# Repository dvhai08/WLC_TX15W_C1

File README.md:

# WLC_TX15W_C1
  Wireless Charging (WLC) MP A11 Power Transmitter
  1. **WLC1115 wireless power Tx simplified diagram**
  
  2. **PCB 3D view**

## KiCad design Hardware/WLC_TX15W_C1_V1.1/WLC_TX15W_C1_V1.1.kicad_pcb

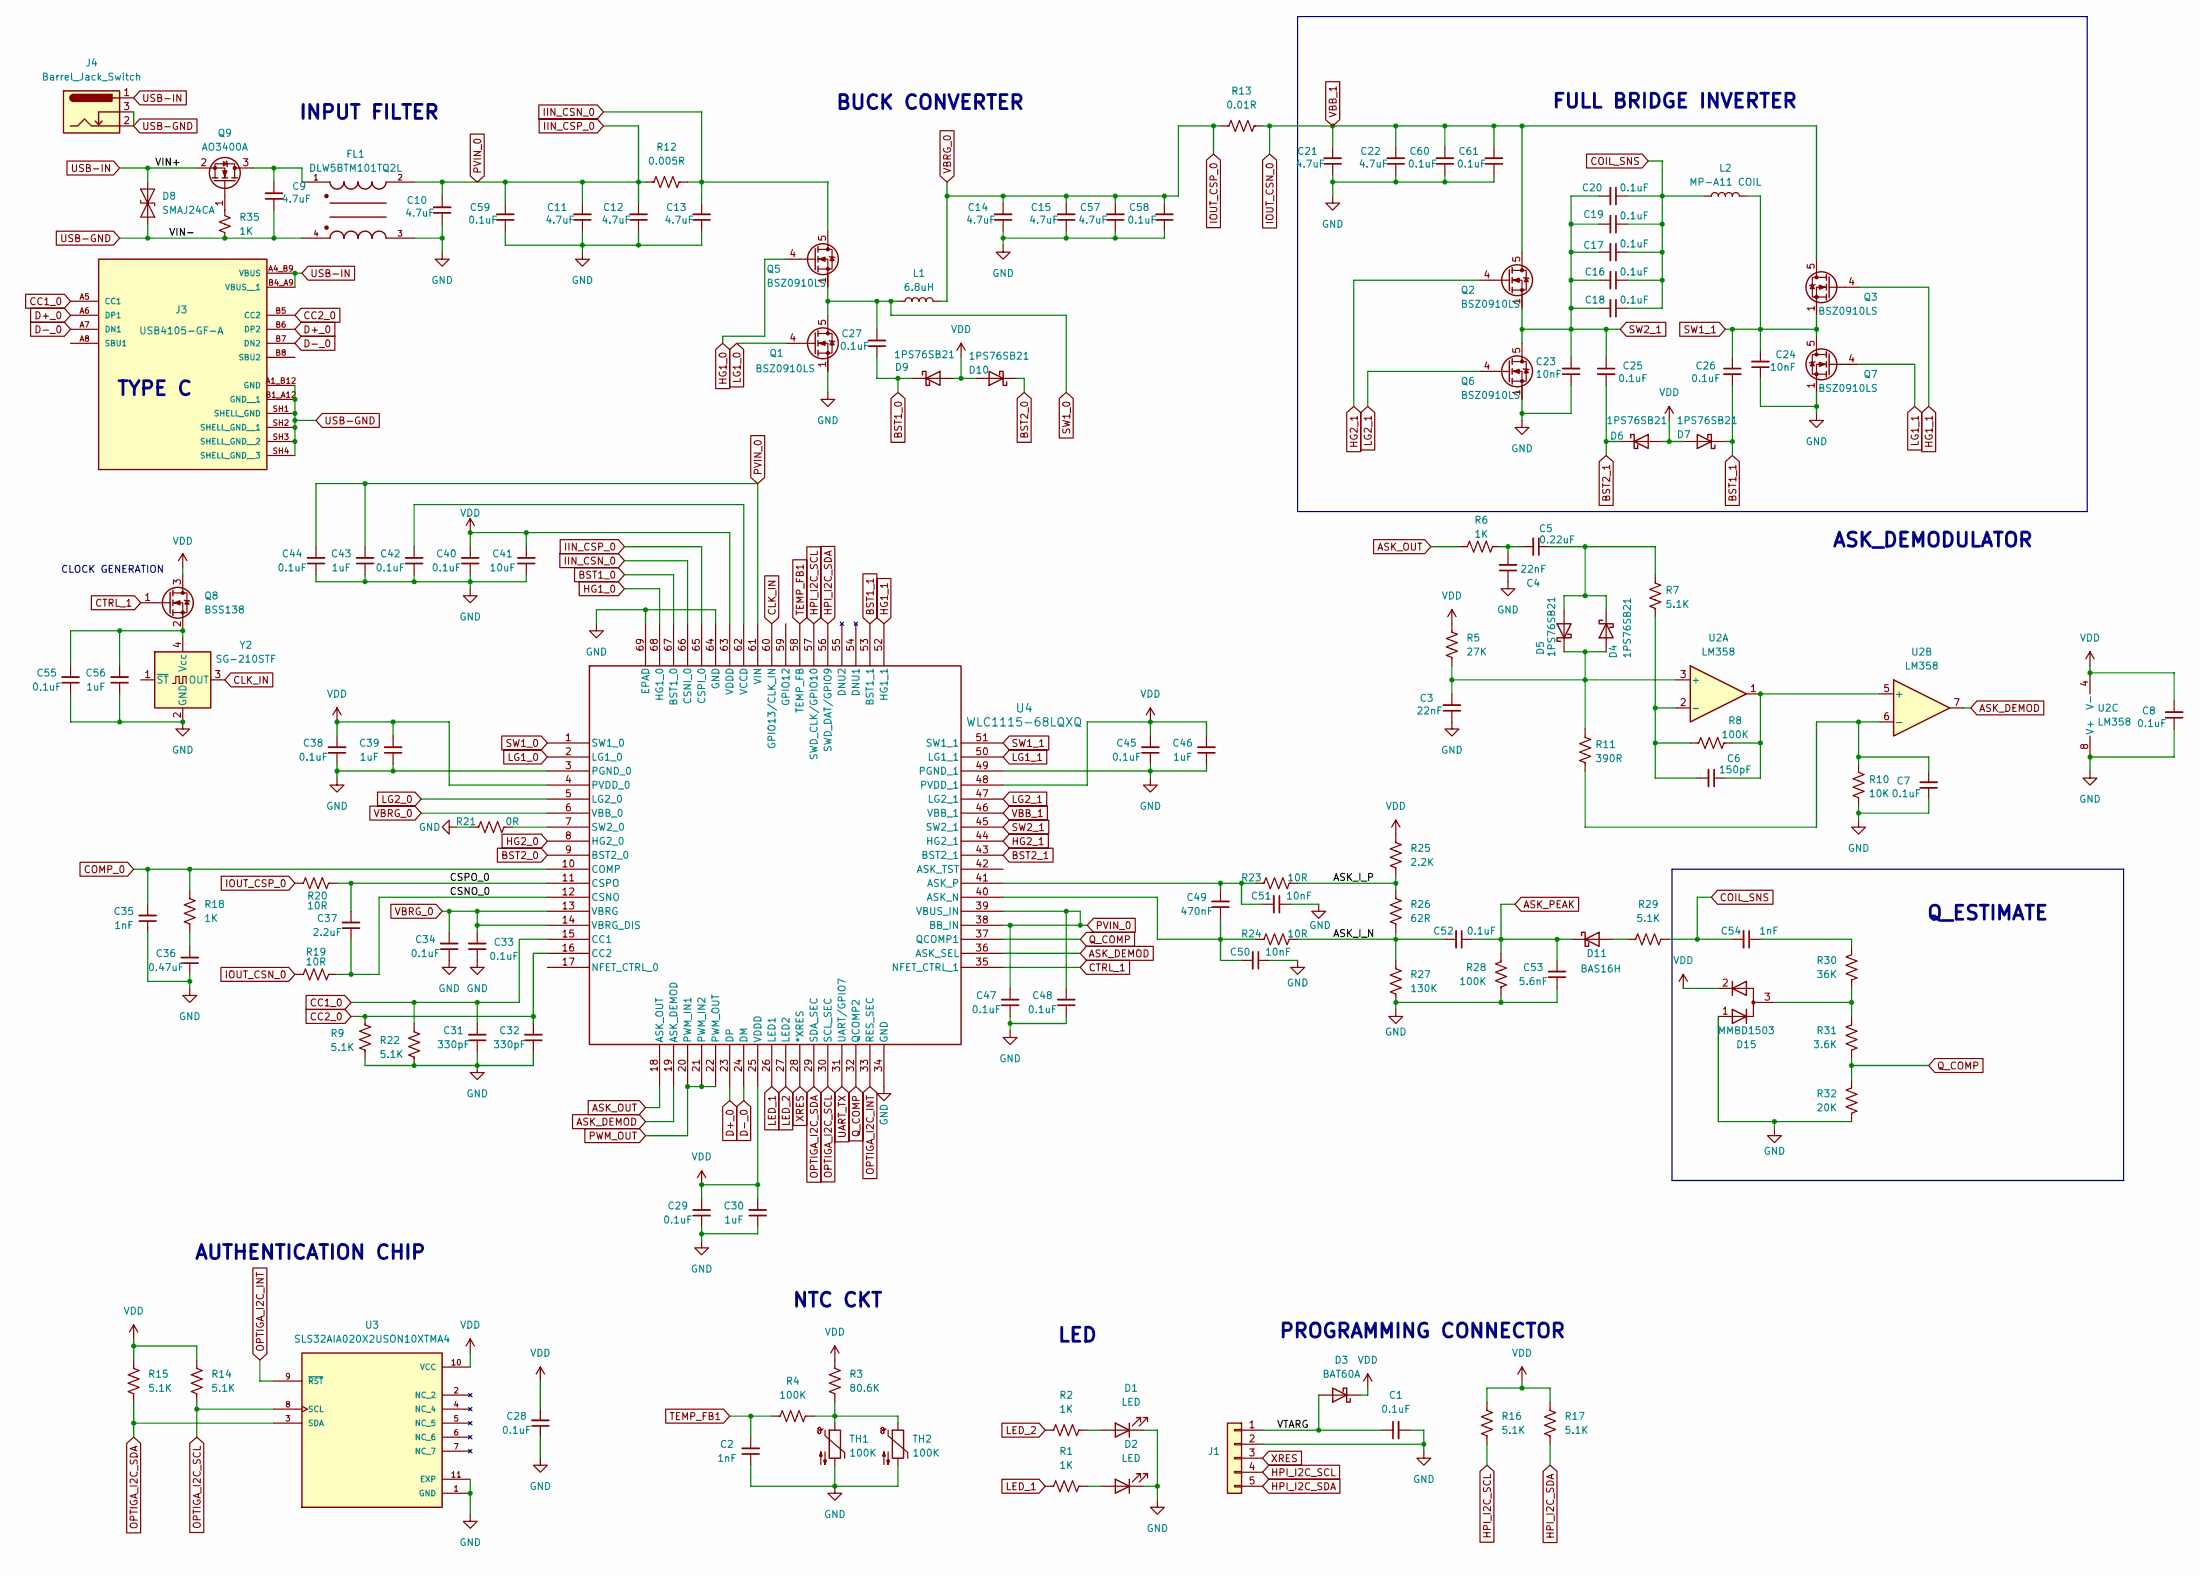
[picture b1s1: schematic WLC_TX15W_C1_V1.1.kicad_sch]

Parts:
C1, C7, C8, C25, C26, C27, C28, C29, C33, C34, C38, C40, C42, C44, C45, C47, C48, C52, C55, C58, C59, C60, C61: 0.1uF; C_0402_1005Metric
C2, C35, C54: 1nF; C_0603_1608Metric
C3, C4: 22nF; C_0402_1005Metric
C5: 0.22uF; C_0402_1005Metric
C6: 150pF; C_0402_1005Metric
C9, C10, C11, C12, C13, C14, C15, C21, C22, C57: 4.7uF; C_0603_1608Metric
C16, C17, C18, C19, C20: 0.1uF; C_1206_3216Metric
C23, C24, C50, C51: 10nF; C_0603_1608Metric
C30, C39, C43, C46, C56: 1uF; C_0603_1608Metric
C31, C32: 330pF; C_0402_1005Metric
C36: 0.47uF; C_0603_1608Metric
C37: 2.2uF; C_0603_1608Metric
C41: 10uF; C_0603_1608Metric
C49: 470nF; C_0603_1608Metric
C53: 5.6nF; C_0603_1608Metric
D1, D2: LED; LED_0603_1608Metric
D3: BAT60A; D_SOD-323
D4, D5, D6, D7, D9, D10: 1PS76SB21; D_SOD-323F
D8: SMAJ24CA; D_SMA
D11: BAS16H; D_SOD-123F
D15: MMBD1503; SOT-23
FL1: DLW5BTM101TQ2L; FIL_DLW5BTM101TQ2L; PARTREV N/A
J1: Conn_01x05; PinHeader_1x05_P2.54mm_Vertical
J3: USB4105-GF-A; GCT_USB4105-GF-A; PARTREV B4
J4: Barrel_Jack_Switch; BarrelJack_GCT_DCJ200-10-A_Horizontal
L1: 6.8uH; L_Bourns-SRN8040_8x8.15mm
L2: MP-A11 COIL; TerminalBlock_bornier-2_P5.08mm
Q1, Q2, Q3, Q5, Q6, Q7: BSZ0910LS; IFX-PG-TSDSON-8-26-V
Q8: BSS138; SOT-23
Q9: AO3400A; SOT-23
R1, R2, R6, R18, R35: 1K; R_0402_1005Metric
R3: 80.6K; R_0402_1005Metric
R4, R8, R28: 100K; R_0402_1005Metric
R5: 27K; R_0402_1005Metric
R7, R9, R14, R15, R16, R17, R22, R29: 5.1K; R_0402_1005Metric
R10: 10K; R_0402_1005Metric
R11: 390R; R_0603_1608Metric
R12: 0.005R; R_1206_3216Metric
R13: 0.01R; R_1206_3216Metric
R19, R20, R23, R24: 10R; R_0402_1005Metric
R21: 0R; R_0402_1005Metric
R25: 2.2K; R_0603_1608Metric
R26: 62R; R_0603_1608Metric
R27: 130K; R_0402_1005Metric
R30: 36K; R_0603_1608Metric
R31: 3.6K; R_0603_1608Metric
R32: 20K; R_0603_1608Metric
TH1: 100K; R_0402_1005Metric
TH2: 100K; R_0805_2012Metric
U2: LM358; SOIC-8_3.9x4.9mm_P1.27mm
U3: SLS32AIA020X2USON10XTMA4; SON50P300X300X60-11N; PARTREV 2.6
U4: WLC1115-68LQXQ; PG-VQFN-68
Y2: SG-210STF; Oscillator_SMD_SeikoEpson_SG210-4Pin_2.5x2.0mm

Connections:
/ASK_I_N: C52.2, R24.1, R26.2, R27.1
/ASK_I_P: R23.1, R25.2, R26.1
/CSNO_0: C37.1, R19.1, U4.12 (CSNO)
/CSPO_0: C37.2, R20.1, U4.11 (CSPO)
/VTARG: C1.1, D3.2 (A), J1.1
ASK_DEMOD: U2.7, U4.19 (ASK_DEMOD), U4.36 (ASK_SEL)
ASK_OUT: R6.1, U4.18 (ASK_OUT)
ASK_PEAK: C52.1, C53.2, D11.1 (K), R28.1
BST1_0: C27.1, D9.1 (K), U4.67 (BST1_0)
BST1_1: C26.2, D7.1 (K), U4.53 (BST1_1)
BST2_0: D10.1 (K), U4.9 (BST2_0)
BST2_1: C25.2, D6.1 (K), U4.43 (BST2_1)
CC1_0: C31.2, J3.A5 (CC1), R22.2, U4.15 (CC1)
CC2_0: C32.2, J3.B5 (CC2), R9.2, U4.16 (CC2)
CLK_IN: U4.60 (GPIO13/CLK_IN), Y2.3 (OUT)
COIL_SNS: C16.1, C17.1, C18.1, C19.1, C20.1, C54.2, L2.1, R29.2
COMP_0: C35.2, R18.2, U4.10 (COMP)
CTRL_1: Q8.1 (G), U4.35 (NFET_CTRL_1)
D+_0: J3.A6 (DP1), J3.B6 (DP2), U4.23 (DP)
D-_0: J3.A7 (DN1), J3.B7 (DN2), U4.24 (DM)
GND: C1.2, C2.1, C3.1, C4.1, C7.1, C8.1, C10.1, C11.1, C12.1, C13.1, C14.1, C15.1, C21.1, C22.1, C23.1, C24.1, C28.1, C29.1, C30.1, C31.1, C32.1, C33.1, C34.1, C35.1, C36.1, C38.1, C39.1, C40.1, C41.1, C42.1, C43.1, C44.1, C45.1, C46.1, C47.1, C48.1, C50.1, C51.1, C53.1, C55.1, C56.1, C57.1, C58.1, C59.1, C60.1, C61.1, D1.1 (K), D2.1 (K), D15.1 (A), FL1.3, J1.2, Q1.1 (S), Q1.2 (S), Q1.3 (S), Q6.1 (S), Q6.2 (S), Q6.3 (S), Q7.1 (S), Q7.2 (S), Q7.3 (S), R9.1, R10.1, R21.2, R22.1, R27.2, R28.2, R32.2, TH1.2, TH2.2, U2.8 (V+), U3.1 (GND), U3.11 (EXP), U4.3 (PGND_0), U4.34 (GND), U4.49 (PGND_1), U4.64 (GND), U4.69 (EPAD), Y2.2 (GND)
HG1_0: Q5.4 (G), U4.68 (HG1_0)
HG1_1: Q3.4 (G), U4.52 (HG1_1)
HG2_0: U4.8 (HG2_0)
HG2_1: Q2.4 (G), U4.44 (HG2_1)
HPI_I2C_SCL: J1.4, R16.1, U4.57 (SWD_CLK/GPIO10)
HPI_I2C_SDA: J1.5, R17.1, U4.56 (SWD_DAT/GPIO9)
IIN_CSN_0: C13.2, Q5.5 (D), Q5.6 (D), Q5.7 (D), Q5.8 (D), R12.1, U4.66 (CSNI_0)
IIN_CSP_0: C10.2, C11.2, C12.2, C43.2, C44.2, C47.2, C48.2, C59.2, FL1.2, R12.2, U4.38 (BB_IN), U4.39 (VBUS_IN), U4.61 (VIN), U4.65 (CSPI_0)
IOUT_CSN_0: C21.2, C22.2, C60.2, C61.2, Q2.5 (D), Q2.6 (D), Q2.7 (D), Q2.8 (D), Q3.5 (D), Q3.6 (D), Q3.7 (D), Q3.8 (D), R13.1, R19.2, U4.46 (VBB_1)
IOUT_CSP_0: C14.2, C15.2, C33.2, C34.2, C57.2, C58.2, L1.2, R13.2, R20.2, U4.6 (VBB_0), U4.13 (VBRG), U4.14 (VBRG_DIS)
LED_1: R1.1, U4.26 (LED1)
LED_2: R2.1, U4.27 (LED2)
LG1_0: Q1.4 (G), U4.2 (LG1_0)
LG1_1: Q7.4 (G), U4.50 (LG1_1)
LG2_0: U4.5 (LG2_0)
LG2_1: Q6.4 (G), U4.47 (LG2_1)
unnamed: C4.2, C5.2, R6.2
unnamed: C36.2, R18.1
unnamed: C54.1, R30.1
unnamed: D1.2 (A), R2.2
unnamed: D2.2 (A), R1.2
unnamed: C3.2, D4.2 (A), D5.1 (K), R5.2, R11.2, U2.3 (+)
unnamed: C5.1, D4.1 (K), D5.2 (A), R7.2
unnamed: D11.2 (A), R29.1
unnamed: D15.3 (common), R30.2, R31.1
unnamed: C55.2, C56.2, Q8.2 (S), Y2.4 (Vcc)
unnamed: C9.2, FL1.1, Q9.3 (D)
unnamed: Q9.1 (G), R35.1
unnamed: R3.1, R4.1, TH1.1, TH2.1
unnamed: C6.2, R7.1, R8.2, U2.2 (-)
unnamed: C6.1, R8.1, U2.1, U2.5 (+)
unnamed: C7.2, R10.2, R11.1, U2.6 (-)
unnamed: C49.1, C50.2, R24.2, U4.40 (ASK_N)
unnamed: C49.2, C51.2, R23.2, U4.41 (ASK_P)
unnamed: R21.1, U4.7 (SW2_0)
unnamed: C42.2, U4.62 (VCCD)
OPTIGA_I2C_INT: U3.9 (~RST), U4.33 (RES_SEC)
OPTIGA_I2C_SCL: R14.1, U3.8 (SCL), U4.30 (SCL_SEC)
OPTIGA_I2C_SDA: R15.1, U3.3 (SDA), U4.29 (SDA_SEC)
PWM_OUT: U4.20 (PWM_IN1), U4.21 (PWM_IN2), U4.22 (PWM_OUT)
Q_COMP: R31.2, R32.1, U4.32 (QCOMP2), U4.37 (QCOMP1)
SW1_0: C27.2, L1.1, Q1.5 (D), Q1.6 (D), Q1.7 (D), Q1.8 (D), Q5.1 (S), Q5.2 (S), Q5.3 (S), U4.1 (SW1_0)
SW1_1: C24.2, C26.1, L2.2, Q3.1 (S), Q3.2 (S), Q3.3 (S), Q7.5 (D), Q7.6 (D), Q7.7 (D), Q7.8 (D), U4.51 (SW1_1)
SW2_1: C16.2, C17.2, C18.2, C19.2, C20.2, C23.2, C25.1, Q2.1 (S), Q2.2 (S), Q2.3 (S), Q6.5 (D), Q6.6 (D), Q6.7 (D), Q6.8 (D), U4.45 (SW2_1)
TEMP_FB1: C2.2, R4.2, U4.58 (TEMP_FB)
UART_TX: U4.31 (UART/GPIO7)
USB-GND: C9.1, D8.1 (A1), FL1.4, J3.A1_B12 (GND), J3.B1_A12 (GND__1), J3.SH1 (SHELL_GND), J3.SH2 (SHELL_GND__1), J3.SH3 (SHELL_GND__2), J3.SH4 (SHELL_GND__3), J4.2, J4.3, R35.2
USB-IN: D8.2 (A2), J3.A4_B9 (VBUS), J3.B4_A9 (VBUS__1), J4.1, Q9.2 (S)
VDD: C8.2, C28.2, C29.2, C30.2, C38.2, C39.2, C40.2, C41.2, C45.2, C46.2, D3.1 (K), D6.2 (A), D7.2 (A), D9.2 (A), D10.2 (A), D15.2 (K), Q8.3 (D), R3.2, R5.1, R14.2, R15.2, R16.2, R17.2, R25.1, U2.4 (V-), U3.10 (VCC), U4.4 (PVDD_0), U4.25 (VDDD), U4.48 (PVDD_1), U4.63 (VDDD)
XRES: J1.3, U4.28 (*XRES)

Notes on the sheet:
BUCK CONVERTER
CLOCK GENERATION
TYPE C
ASK_DEMODULATOR
INPUT FILTER
NTC CKT
LED
FULL BRIDGE INVERTER
AUTHENTICATION CHIP
Q_ESTIMATE
PROGRAMMING CONNECTOR

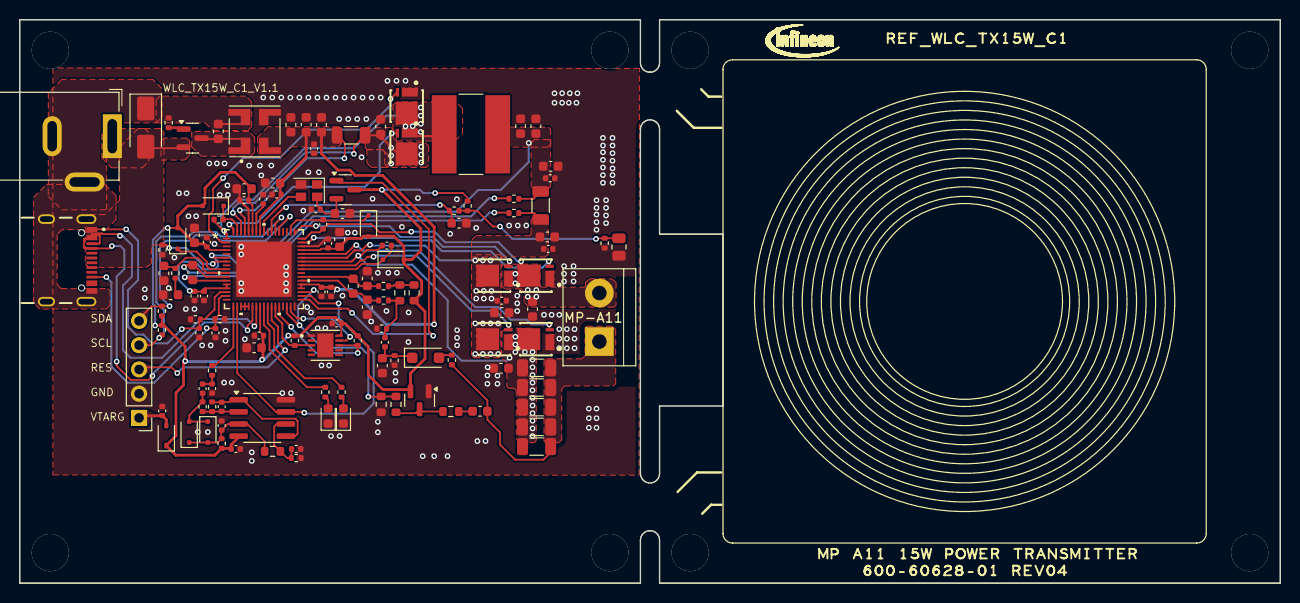
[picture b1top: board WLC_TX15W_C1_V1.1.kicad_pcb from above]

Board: 2 copper layers, 132.0 x 59.0 mm, 126 parts (0 on the bottom side), 68 nets.

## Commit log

2025-05-27 add schematic
2025-05-28 add simplified diagram
2025-05-28 add usb type c
2025-05-29 update bom
2025-05-30 Fix board outline
